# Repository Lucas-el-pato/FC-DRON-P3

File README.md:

# FC-DRON-P3 - P4
PCB para Control de vuelo de un Dron para la materia de Proyecto 3 y Proyecto 4 por Lucas Garcia e Hernan Ibarra

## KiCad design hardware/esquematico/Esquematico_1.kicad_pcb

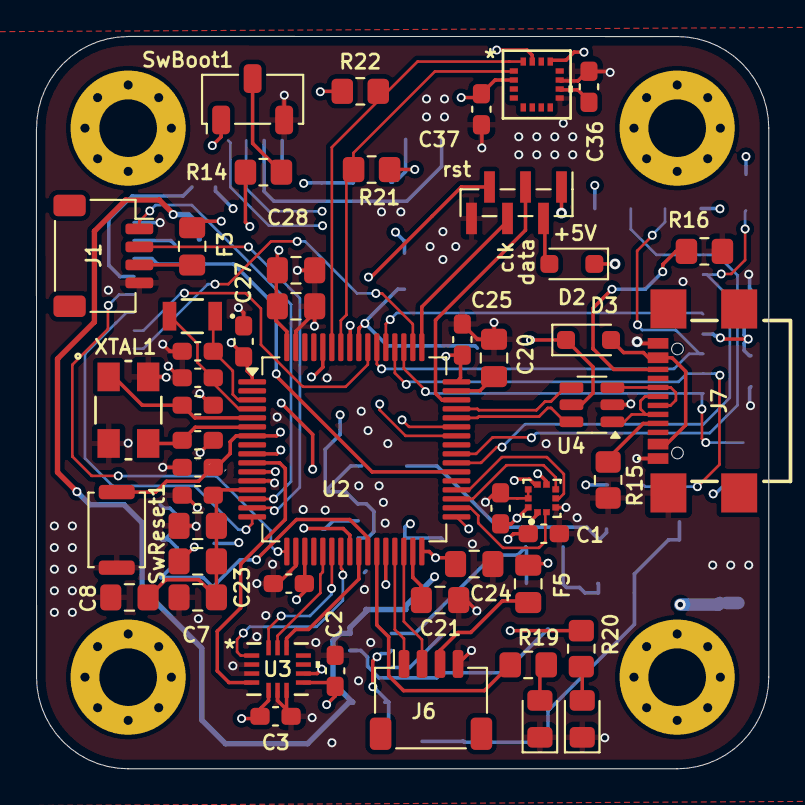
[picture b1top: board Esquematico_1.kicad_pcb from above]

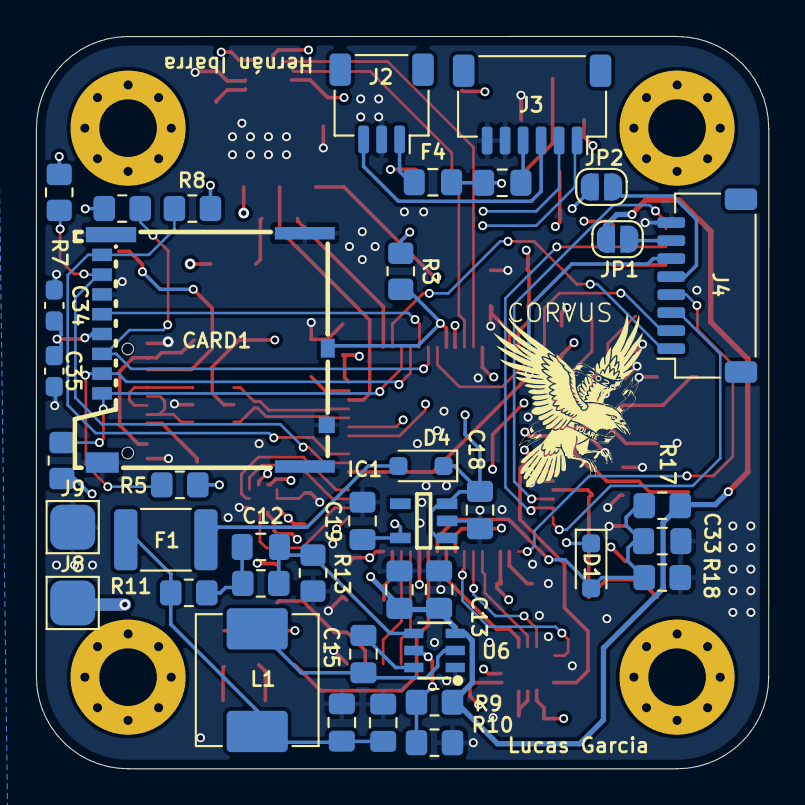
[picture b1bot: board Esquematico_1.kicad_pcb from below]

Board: 6 copper layers, 40.7 x 40.7 mm, 94 parts (40 on the bottom side), 77 nets.

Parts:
C1, C2, C3, C4, C22, C23, C25, C27, C32, C35: 100nF; C_0603_1608Metric_Pad1.08x0.95mm_HandSolder
C5, C6: 15pF; C_0603_1608Metric_Pad1.08x0.95mm_HandSolder
C7, C14: 10uF; C_0805_2012Metric_Pad1.18x1.45mm_HandSolder
C8, C13, C15, C24, C26, C33: 100nF; C_0805_2012Metric_Pad1.18x1.45mm_HandSolder
C12: 75pF; C_0805_2012Metric_Pad1.18x1.45mm_HandSolder
C16, C17: 22uF; C_0805_2012Metric_Pad1.18x1.45mm_HandSolder
C18, C19, C29: 1uF; C_0805_2012Metric_Pad1.18x1.45mm_HandSolder
C20, C21: 2.2uF; C_0805_2012Metric_Pad1.18x1.45mm_HandSolder
C28: 4.7u; C_0805_2012Metric_Pad1.18x1.45mm_HandSolder
C30, C31: 12pF; C_0603_1608Metric_Pad1.08x0.95mm_HandSolder
C34: 10uF; C_0603_1608Metric_Pad1.08x0.95mm_HandSolder
C36: 10 nF; C_0603_1608Metric_Pad1.08x0.95mm_HandSolder
C37: 1 uF; C_0603_1608Metric_Pad1.08x0.95mm_HandSolder
CARD1: MICRO SD; TF-SMD_503398-1892
D1, D3, D4: D_Schottky; D_SOD-323_HandSoldering
D2: D_ST; D_SOD-323_HandSoldering
D7, D8: LED; LED_0805_2012Metric_Pad1.15x1.40mm_HandSolder
F1: 2.5A; Fuse_1812_4532Metric_Pad1.30x3.40mm_HandSolder
F2, F3, F4, F5: 750mA; C_0805_2012Metric_Pad1.18x1.45mm_HandSolder
FB1: FerriteBead; C_0805_2012Metric_Pad1.18x1.45mm_HandSolder
H1, H2, H3, H4: MountingHole; MountingHole_3.2mm_M3_Pad_Via
IC1: AP2112K-3.3TRG1; SOT95P285X140-5N
J1, J6: Screw_Terminal_01x04; JST_SH_SM04B-SRSS-TB_1x04-1MP_P1.00mm_Horizontal
J2: Screw_Terminal_01x03; JST_SH_SM03B-SRSS-TB_1x03-1MP_P1.00mm_Horizontal
J3: Screw_Terminal_01x06; JST_SH_SM06B-SRSS-TB_1x06-1MP_P1.00mm_Horizontal
J4: Screw_Terminal_01x08; JST_SH_SM08B-SRSS-TB_1x08-1MP_P1.00mm_Horizontal
J5: SWD; PinHeader_1x06_P1.00mm_Vertical_SMD_Pin1Left
J7: USB_C_Receptacle_USB2.0_16P; USB494000A
J8, J9: Screw_Terminal_01x01; TestPoint_Pad_2.5x2.5mm
JP1, JP2: SolderJumper_2_Open; SolderJumper-2_P1.3mm_Open_RoundedPad1.0x1.5mm
L1: 10uH; L_KOHERelec_MDA7030
LSE1: Crystal; XTAL_NX3215SA_NDK
R3, R12, R17: 100k; R_0805_2012Metric_Pad1.20x1.40mm_HandSolder
R4, R5, R6, R7, R8: 47K; R_0805_2012Metric_Pad1.20x1.40mm_HandSolder
R9: 511K; R_0805_2012Metric_Pad1.20x1.40mm_HandSolder
R10: 105K; R_0805_2012Metric_Pad1.20x1.40mm_HandSolder
R11: 49.9; R_0805_2012Metric_Pad1.20x1.40mm_HandSolder
R13: 13.3K; R_0805_2012Metric_Pad1.20x1.40mm_HandSolder
R14: 10k; R_0805_2012Metric_Pad1.20x1.40mm_HandSolder
R15, R16: 5k1; R_0805_2012Metric_Pad1.20x1.40mm_HandSolder
R18: 15k; R_0805_2012Metric_Pad1.20x1.40mm_HandSolder
R19, R20: 330; R_0805_2012Metric_Pad1.20x1.40mm_HandSolder
R21, R22: 2.7K; R_0805_2012Metric_Pad1.20x1.40mm_HandSolder
SwBoot1: SW_Nidec_CAS-120A1; Nidec_Copal_CAS-120A
SwReset1: SW_Push; SW_Push_SPST_NO_Alps_SKRK
U2: STM32F405RGTx; LQFP-64_10x10mm_P0.5mm
U3: LSM6DSV16XTR; LGA-14L_STM
U4: BMP388; PQFN50P200X200X80-10N
U5: USBLC6-2SC6; SOT-23-6
U6: TPS54302DDCR; SOT-23-6_L2.9-W1.6-P0.95-LS2.8-BL
U7: MMC5983MA; MMC5983MA_MEM
XTAL1: ECS-80-12-30BQ-JES-TR; ECS-80-12_ECS

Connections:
+3V3: C1.1, C2.1, C3.1, C4.1, C19.2, C23.1, C24.1, C25.1, C26.1, C27.1, C28.1, C34.2, C35.2, C37.1, CARD1.4 (VDD), D1.1 (K), D2.1 (K), F5.2, FB1.1, IC1.5 (VOUT), R3.1, R4.1, R5.1, R6.1, R7.1, R8.1, R21.1, R22.1, SwBoot1.1 (C), U2.1 (VBAT), U2.19 (VDD), U2.32 (VDD), U2.48 (VDD), U2.64 (VDD), U3.5 (VDD_IO), U3.8 (VDD), U4.1 (VDDIO), U4.10 (VDD), U7.2 (VDD), U7.13 (VDDIO)
+3V3A: C7.2, C8.2, C22.1, C29.1, FB1.2, U2.13 (VDDA)
/JST y CAM/CC1: J7.A5 (CC1), R15.1
/JST y CAM/CC2: J7.B5 (CC2), R16.1
/JST y CAM/D+: J7.A6 (D+), J7.B6 (D+), U5.3 (I/O2)
/JST y CAM/D-: J7.A7 (D-), J7.B7 (D-), U5.1 (I/O1)
/MCU/BOOT0: R14.2, U2.60 (BOOT0)
/MCU/HSE_IN: C6.1, U2.5 (PH0), XTAL1.1
/MCU/HSE_OUT: C5.1, U2.6 (PH1), XTAL1.3
/MCU/LGreen: R20.1, U2.28 (PB2)
/MCU/LRed: R19.1, U2.27 (PB1)
/MCU/LSE_IN: C31.1, LSE1.1, U2.3 (PC14)
/MCU/LSE_OUT: C30.1, LSE1.2, U2.4 (PC15)
AP_CS_IMU: U2.25 (PC5), U3.12 (CS)
Bat_Med_FC: C33.1, D1.2 (A), R17.2, R18.1, U2.26 (PB0)
CLK_BM: U2.34 (PB13), U4.2 (SCK)
CLK_IMU: U2.21 (PA5), U3.13 (SCL)
CRT: JP2.2 (B), U2.24 (PC4)
CS_BM: U2.33 (PB12), U4.6 (CSB)
CardDetect: CARD1.9, R3.2, U2.56 (PB4)
ELRS_UART_RX: J1.2, U2.15 (PA1)
ELRS_UART_TX: J1.1, U2.14 (PA0)
EN: R9.1, R10.2, U6.5 (EN)
ESC1: J4.1, U2.50 (PA15)
ESC2: J4.2, U2.55 (PB3)
ESC3: J4.3, U2.16 (PA2)
ESC4: J4.4, U2.17 (PA3)
GND: C1.2, C2.2, C3.2, C4.2, C5.2, C6.2, C7.1, C8.1, C13.1, C14.1, C16.1, C17.1, C18.1, C19.1, C20.2, C21.2, C22.2, C23.2, C24.2, C25.2, C26.2, C27.2, C28.2, C29.2, C30.2, C31.2, C32.2, C33.2, C34.1, C35.1, C36.2, C37.2, CARD1.6 (VSS), CARD1.10, CARD1.11 (EH), D7.1 (K), D8.1 (K), IC1.2 (GND), J1.4, J2.2, J3.5, J3.6, J4.8, J5.6, J6.4, J7.A1 (GND), J7.B1 (GND), J7.S1 (SHIELD), J9.1, R10.1, R13.2, R15.2, R16.2, R18.2, SwBoot1.3 (A), SwReset1.1, U2.12 (VSSA), U2.18 (VSS), U2.63 (VSS), U3.2 (SDX/AH1/QVAR1), U3.3 (SCX/AH2/QVAR2), U3.6 (GND), U3.7 (GND), U4.3 (VSS), U4.8 (VSS__1), U4.9 (VSS__2), U5.2 (GND), U6.1 (GND), U7.9 (GND), U7.11 (GND), XTAL1.2, XTAL1.4
GPS_UART_RX: J6.2, U2.30 (PB11)
GPS_UART_TX: J6.1, U2.29 (PB10)
INT1_IMU: U2.10 (PC2), U3.4 (INT1)
INT2_IMU: U2.11 (PC3), U3.9 (INT2)
INT_BM: U2.9 (PC1), U4.7 (INT)
INT_MAG: U2.57 (PB5), U7.15 (INT)
LDO_USB: C18.2, D3.1 (K), D4.1 (K), F2.1, F3.2, F4.2, IC1.1 (VIN), IC1.3 (EN), J5.1, U5.5 (VBUS)
MISO_BM: U2.35 (PB14), U4.5 (SDO)
MISO_IMU: U2.22 (PA6), U3.14 (SDA)
MOSI_BM: U2.36 (PB15), U4.4 (SDI)
MOSI_IMU: U2.23 (PA7), U3.1 (SDO/SA0)
unnamed: C12.1, R11.2, R12.1
unnamed: C16.2, C17.2, F1.2, L1.2, R11.1
unnamed: D2.2 (A), J5.2
unnamed: D3.2 (A), J7.A4 (VBUS), J7.B4 (VBUS)
unnamed: D4.2 (A), F1.1
unnamed: D7.2 (A), R20.2
unnamed: D8.2 (A), R19.2
unnamed: F3.1, J1.3
unnamed: F4.1, J2.1
unnamed: F2.2, J3.4
unnamed: J4.5, JP2.1 (A)
unnamed: J4.7, JP1.1 (A)
unnamed: F5.1, J6.3
unnamed: R14.1, SwBoot1.2 (B)
unnamed: C21.1, U2.31 (VCAP_1)
unnamed: C20.1, U2.47 (VCAP_2)
unnamed: C15.1, U6.6 (BOOT)
unnamed: C12.2, R12.2, R13.1, U6.4 (FB)
unnamed: C36.1, U7.10 (CAP)
RX_VTX: J3.2, U2.43 (PA10)
SCL_MAG: R21.2, U2.58 (PB6), U7.1 (SCL/SPI_SCK)
SDA_MAG: R22.2, U2.59 (PB7), U7.16 (SDA/SPI_SDI)
SDIO_CLK: CARD1.5 (CLK), U2.53 (PC12)
SDIO_CMD: CARD1.3 (CMD), R6.2, U2.54 (PD2)
SDIO_D0: CARD1.7 (DAT0), R7.2, U2.39 (PC8)
SDIO_D1: CARD1.8 (DAT1), R8.2, U2.40 (PC9)
SDIO_D2: CARD1.1 (DAT2), R4.2, U2.51 (PC10)
SDIO_D3: CARD1.2 (CD/DAT3), R5.2, U2.52 (PC11)
SW: C15.2, L1.1, U6.2 (SW)
SWCLK: J5.4, U2.49 (PA14)
SWDIO: J5.3, U2.46 (PA13)
SWD_NRST: C32.1, J5.5, SwReset1.2, U2.7 (NRST)
TELEM_ESC: J4.6, U2.38 (PC7)
TX_VTX: J3.1, U2.42 (PA9)
USB_D+: U2.45 (PA12), U5.4 (I/O2)
USB_D-: U2.44 (PA11), U5.6 (I/O1)
VCC: C13.2, C14.2, J8.1, JP1.2 (B), R9.2, R17.1, U6.3 (VIN)
VIDEO: J2.3, J3.3

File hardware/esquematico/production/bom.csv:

Designator,Footprint,Quantity,Value,LCSC Part #
"C1, C2, C22, C23, C25, C27, C3, C32, C35, C4",0603,10,100nF,
C12,0805,1,75pF,
"C13, C15, C24, C26, C33, C8",0805,6,100nF,
"C14, C7",0805,2,10uF,
"C16, C17",0805,2,22uF,
"C18, C19, C29",0805,3,1uF,
"C20, C21",0805,2,2.2uF,
C28,0805,1,4.7u,
"C30, C31",0603,2,12pF,
C34,0603,1,10uF,
C36,0603,1,10 nF,
C37,0603,1,1 uF,
"C5, C6",0603,2,15pF,
CARD1,TF-SMD_503398-1892,1,MICRO SD,
"D1, D3, D4",D_SOD-323_HandSoldering,3,D_Schottky,
D2,D_SOD-323_HandSoldering,1,D_ST,
"D7, D8",0805,2,LED,
F1,1812,1,2.5A,
"F2, F3, F4, F5",0805,4,750mA,
IC1,SOT95P285X140-5N,1,AP2112K-3.3TRG1,
"J1, J6",JST_SH_SM04B-SRSS-TB_1x04-1MP_P1.00mm_Horizontal,2,Screw_Terminal_01x04,
J2,JST_SH_SM03B-SRSS-TB_1x03-1MP_P1.00mm_Horizontal,1,Screw_Terminal_01x03,
J3,JST_SH_SM06B-SRSS-TB_1x06-1MP_P1.00mm_Horizontal,1,Screw_Terminal_01x06,
J4,JST_SH_SM08B-SRSS-TB_1x08-1MP_P1.00mm_Horizontal,1,Screw_Terminal_01x08,
LSE1,XTAL_NX3215SA_NDK,1,Crystal,
R10,0805,1,105K,
R11,0805,1,49.9,
"R12, R17, R3",0805,3,100k,
R13,0805,1,13.3K,
"R15, R16",0805,2,5k1,
R18,0805,1,15k,
R9,0805,1,511K,
SWBOOT1,Nidec_Copal_CAS-120A,1,SW_Nidec_CAS-120A1,
SWRESET1,SW_Push_SPST_NO_Alps_SKRK,1,SW_Push,
U2,LQFP-64_10x10mm_P0.5mm,1,STM32F405RGTx,
U3,LGA-14L_STM,1,LSM6DSV16XTR,
U4,PQFN50P200X200X80-10N,1,BMP388,
U5,SOT-23-6,1,USBLC6-2SC6,
U6,SOT-23-6_L2.9-W1.6-P0.95-LS2.8-BL,1,TPS54302DDCR,
U7,MMC5983MA_MEM,1,MMC5983MA,

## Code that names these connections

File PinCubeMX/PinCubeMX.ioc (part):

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Mcu.Name=STM32F405RGTx
Mcu.Package=LQFP64
Mcu.UserName=STM32F405RGTx
PA0-WKUP.Mode=Asynchronous
PA0-WKUP.Signal=UART4_TX
PA1.Mode=Asynchronous
PA1.Signal=UART4_RX
PA11.Mode=Device_Only
PA11.Signal=USB_OTG_FS_DM
PA12.Mode=Device_Only
PA12.Signal=USB_OTG_FS_DP
PA13.Mode=Serial_Wire
PA13.Signal=SYS_JTMS-SWDIO
PA14.Mode=Serial_Wire
PA14.Signal=SYS_JTCK-SWCLK
PA15.GPIOParameters=GPIO_Label
PA15.GPIO_Label=M4
PA15.Signal=S_TIM2_CH1_ETR
PA2.GPIOParameters=GPIO_Label
PA2.GPIO_Label=M2
PA2.Signal=S_TIM2_CH3
PA3.GPIOParameters=GPIO_Label
PA3.GPIO_Label=M1
PA3.Signal=S_TIM2_CH4
PA5.Mode=Full_Duplex_Master
PA5.Signal=SPI1_SCK
PA6.Mode=Full_Duplex_Master
PA6.Signal=SPI1_MISO
PA7.Mode=Full_Duplex_Master
PA7.Signal=SPI1_MOSI
PB0.Signal=ADCx_IN8
PB1.GPIOParameters=GPIO_Label
PB1.GPIO_Label=led_rojo
PB1.Signal=GPIO_Output
PB10.Mode=Asynchronous
PB10.Signal=USART3_TX
PB11.Mode=Asynchronous
PB11.Signal=USART3_RX
PB12.GPIOParameters=GPIO_PuPd,GPIO_Label
PB12.GPIO_Label=bar_cs
PB12.GPIO_PuPd=GPIO_PULLDOWN
PB12.Signal=GPIO_Output
PB13.Mode=Full_Duplex_Master
PB13.Signal=SPI2_SCK
PB14.Mode=Full_Duplex_Master
PB14.Signal=SPI2_MISO
PB15.Mode=Full_Duplex_Master
PB15.Signal=SPI2_MOSI
PB2.GPIOParameters=GPIO_Label
PB2.GPIO_Label=led_verde
PB2.Signal=GPIO_Output
PB3.GPIOParameters=GPIO_Label
PB3.GPIO_Label=M3
PB3.Signal=S_TIM2_CH2
PB4.GPIOParameters=GPIO_Label
PB4.GPIO_Label=SD_CS
PB4.Signal=GPIO_Input
PB5.Signal=GPIO_Input
PB6.Mode=I2C
PB6.Signal=I2C1_SCL
PB7.Mode=I2C
PB7.Signal=I2C1_SDA
PC1.Signal=GPIO_Input
PC10.Mode=SD_4_bits_Wide_bus
PC10.Signal=SDIO_D2
PC11.Mode=SD_4_bits_Wide_bus
PC11.Signal=SDIO_D3
PC12.Mode=SD_4_bits_Wide_bus
PC12.Signal=SDIO_CK
PC14-OSC32_IN.Mode=LSE-External-Oscillator
PC14-OSC32_IN.Signal=RCC_OSC32_IN
PC15-OSC32_OUT.Mode=LSE-External-Oscillator
PC15-OSC32_OUT.Signal=RCC_OSC32_OUT
PC2.GPIOParameters=GPIO_PuPd,GPIO_Label
PC2.GPIO_Label=Gyro_Data
PC2.GPIO_PuPd=GPIO_NOPULL
PC2.Signal=GPXTI2
PC4.Signal=ADCx_IN14
PC5.Signal=GPIO_Output
PC6.Mode=Asynchronous
PC6.Signal=USART6_TX
PC7.GPIOParameters=GPIO_PuPd
PC7.GPIO_PuPd=GPIO_NOPULL
PC7.Mode=Asynchronous
PC7.Signal=USART6_RX
PC8.Mode=SD_4_bits_Wide_bus
PC8.Signal=SDIO_D0
PC9.Mode=SD_4_bits_Wide_bus
PC9.Signal=SDIO_D1
PD2.Mode=SD_4_bits_Wide_bus
PD2.Signal=SDIO_CMD
PH0-OSC_IN.Mode=HSE-External-Oscillator
PH0-OSC_IN.Signal=RCC_OSC_IN
PH1-OSC_OUT.Mode=HSE-External-Oscillator
PH1-OSC_OUT.Signal=RCC_OSC_OUT
RCC.HSE_VALUE=8000000
RCC.SYSCLKFreq_VALUE=168000000
RCC.SYSCLKSource=RCC_SYSCLKSOURCE_PLLCLK
board=custom

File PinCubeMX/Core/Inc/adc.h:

/* USER CODE BEGIN Header */
/**
  ******************************************************************************
  * @file    adc.h
  * @brief   This file contains all the function prototypes for
  *          the adc.c file
  ******************************************************************************
  * @attention
  *
  * Copyright (c) 2026 STMicroelectronics.
  * All rights reserved.
  *
  * This software is licensed under terms that can be found in the LICENSE file
  * in the root directory of this software component.
  * If no LICENSE file comes with this software, it is provided AS-IS.
  *
  ******************************************************************************
  */
/* USER CODE END Header */
/* Define to prevent recursive inclusion -------------------------------------*/
#ifndef __ADC_H__
#define __ADC_H__

#ifdef __cplusplus
extern "C" {
#endif

/* Includes ------------------------------------------------------------------*/
#include "main.h"

/* USER CODE BEGIN Includes */

/* USER CODE END Includes */

extern ADC_HandleTypeDef hadc1;

/* USER CODE BEGIN Private defines */

/* CRT (ESC amp sense) -> PC4 / ADC1_IN14. Escala fabricante: 11.75 mV/A. */
#define ADC_CRT_CHANNEL          ADC_CHANNEL_14
#define ADC_CRT_MV_PER_A_X100    1175u  /* 11.75 mV/A * 100 */
#define ADC_VREF_MV              3300u
#define ADC_MAX_COUNTS           4095u

/* VBAT -> PB0 / ADC1_IN8 (net Bat_Med_FC, divisor R17 100k / R18 15k). */
#define ADC_VBAT_CHANNEL         ADC_CHANNEL_8

/* USER CODE END Private defines */

void MX_ADC1_Init(void);

/* USER CODE BEGIN Prototypes */

/* Lectura blocking del pin CRT (PC4). Devuelve counts 12-bit o 0xFFFF si falla. */
uint16_t adc_crt_read_raw(void);

/* Convierte counts ADC a centiamperios (100 = 1.00 A). raw 0xFFFF -> 0. */
uint16_t adc_crt_raw_to_ca(uint16_t raw);

/* Corriente CRT en centiamperios (100 = 1.00 A). */
uint16_t adc_crt_read_ca(void);

/* Lectura blocking del divisor de bateria (PB0). Counts 12-bit o 0xFFFF. */
uint16_t adc_vbat_read_raw(void);

/* USER CODE END Prototypes */

#ifdef __cplusplus
}
#endif

#endif /* __ADC_H__ */

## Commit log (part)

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2026-02-21 Added Diagrama de bloques FC Dron.drawio.svg
2026-02-21 Carga de esquematico
    prueba de carga de esquematico
2026-02-21 Add file patterns to .gitignore
    Ignora tipos de archivos generados por kicad para que no sea demasiado pesado
2026-02-21 Testing add a MCU
2026-02-21 carga de algunos datasheets y footprints
2026-02-21 Esquematico 2 en kicad 10
    kicad 10, pruba del footprint y esqumatico del magnetometro descargando en formato altium
2026-02-21 Carga de esqumaticos
    Carga de esquematicos
    GPS
    GYRO
    MAG
    BARO
    USB
2026-02-21 Nueva carga de esquematicos y footprints
2026-02-21 Se agregaron las páginas para el trabajo
2026-02-23 Carga de esquematicos y footprint para kicad 9
2026-02-23 Carga de footprints
2026-02-23 Kicad changes
2026-02-24 Conexion esqumatica del Magnetometro
2026-02-24 Conexionado esquematico del Barometro
2026-02-24 Conexion esquematica Micro SD
2026-02-24 Update Micro SD
2026-02-24 Descripcion de esquematicos
2026-02-24 Update Descricion de esquematicos
2026-02-24 General aplication and ICM footprint
2026-02-25 Update esquematico
2026-02-25 Update squematic
2026-02-25 OSD added
2026-02-25 Update de algo nsq que puta
2026-02-25 Update Power
2026-02-26 Update footprint library
2026-02-26 Cambios menores nada relevante
2026-02-27 Update Diagrama de bloques FC Dron
2026-02-27 Diagrama de bloques FC Dron.drawio.svg
2026-02-27 Chau OSD
2026-02-28 Actualización MCU, se colocaron correctamente los capacitores de desacoplo
2026-03-01 Cristales y algunas correciones
2026-03-01 Correciones de tags
2026-03-02 Inlcluí el SW
2026-03-02 UBS, botón de reset y boot, también por fin SWD
2026-03-02 Descripciones
2026-03-02 Cambio de ESC
2026-03-02 aplication notes
2026-03-03 Cristales y arreglo de los simbolos que no estaban en referencia
2026-03-03 Cambios
2026-03-05 Update Circuito de medicion de bateria
2026-03-06 Conexiones con MCU, IMU, VTX, ELRS y Magnometro
2026-03-06 Actualizaciones del PinCube
2026-03-08 último sensor conectado, y le quité los colores al net_signal xdd
2026-03-08 Update llamada
2026-03-08 Update Fisubles
2026-03-09 Cambios insignificantes
2026-03-10 Cambio del cristal por n-ésima vez
2026-03-10 Actualizacion de PinCubeMX
2026-03-10 Update polyfuse
2026-03-10 asignación de footprints
2026-03-10 Footprints
2026-03-10 Update Footprint sw reset
2026-03-10 Update footprint sw rst
2026-03-10 USB 16 Pin
2026-03-10 LDS y gran corrección de errores del esquemático
2026-03-11 pequeños cambios
2026-03-11 Todos los footprints menos ESC
2026-03-11 Update pcb
2026-03-11 Update PCB y JST
2026-03-12 Cambios netclasses, rules en el PCB, conección de los cristales
2026-03-12 Actualizacion
2026-03-13 BIG Update conexionado MCU y PCB
2026-03-13 Big uptdate
2026-03-13 Push prueba PCB LUCAS
2026-03-13 Diodo de mierda
2026-03-13 Update PCB backlayer
2026-03-13 update pcb lucas
2026-03-13 Cristal corregido
2026-03-14 Re ubicación de componentes,falta IMU, MAG y ferrita
2026-03-14 Update buck y LDO
2026-03-14 Update kilombo
2026-03-14 Magnometro listo y luces led
2026-03-14 Reposicionamiento de los LEDS jjji
2026-03-14 Update version con magnometro
2026-03-14 Update conectado el cir. med. de bat
2026-03-15 Update ruteado PCB
2026-03-15 Update nsq puta
2026-03-15 Corrección pistas de 90 grados y Power plane 3,3V
2026-03-15 Re ordenar para hacer el fucking SPI del IMU
2026-03-16 Re size la placa, obs verificar el tamaño xd, solamente falta USB y VCC
2026-03-16 Update arreglo de errores
2026-03-16 Update pcb 0 errores
    8========D
2026-03-16 Pequeños retoques de los nombres
2026-03-16 Add 3d model pa
2026-03-17 Cambio de la SD, re ruteo del ESC para mayor fiabilidad, correción en el clearence
2026-03-17 Cambios menores
2026-03-19 Correcciones menores
2026-03-19 Eliminacion de carpeta Esquematico_2
2026-03-20 Cambios de Diodos
2026-03-27 Correccion de tamaño
2026-03-27 Asesinato de cantos
2026-03-28 Cambios de todas las vías
2026-03-29 Cambio de magnometro :c
2026-03-29 simplemente una actualizacion del PinCUbe
2026-04-01 Cambio de IMU, creación del BOM
2026-04-16 Pequeños cambios en los silkscreen
2026-04-18 Silkscreen y huellas en general de la imagenes
2026-04-21 crow
2026-04-21 crow final
2026-04-22 Correccion final
    2 hermana
2026-04-22 error fixed
2026-04-22 USB fix
2026-04-23 ultimo retoque final
2026-05-27 Commit toqueteo: todo menos ELRS y Motor y SD
2026-06-01 MicroSD
2026-06-11 Dashboard
